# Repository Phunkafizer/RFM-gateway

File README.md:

<p align="center">

</p>

# RFM Gateway

RFM Gateway is a radio-to-WiFi bridge that connects HopeRF radio modules to an
ESP8266. It can receive RF data and forward it to your WiFi network, and it can
also send RF commands from HTTP or MQTT inputs.

Project description:
https://www.seegel-systeme.de/2023/09/15/rfm-wifi-gateway-a-radio-to-wifi-bridge/

Home Assistant forum:
https://community.home-assistant.io/t/rfm-gateway-a-sub-ghz-bridge-to-home-assistant/982886

## Highlights

- USB-C for power, flashing, and UART access
- Integrated USB programmer (no extra external programmer required)
- SMA antenna connector for the radio module
- Optional 0.96 inch I2C OLED support
- I2C and 1-wire extension headers

## Firmware capabilities

- 433 MHz RC pulse gateway (receive and transmit)
- 868 MHz sensor gateway (for supported sensor families)
- 868 MHz FS20 gateway
- Home Assistant integration via MQTT discovery

## Typical applications

- Bring wireless weather sensors into WiFi and MQTT
- Control RF sockets and remote controls
- Bridge RF nodes into home automation systems

## Repository structure

- [Firmware/](Firmware/): PlatformIO firmware project and web UI
- [custom_components/rfm_gateway/](custom_components/rfm_gateway/): Home Assistant custom integration
- [PCB/](PCB/): hardware design files
- [assets/](assets/): screenshots and images

## Home Assistant custom integration

The RFM Gateway integration connects Home Assistant directly to the gateway's
local HTTP API and provides a radio frequency transmitter. MQTT is not required
for this integration.

### Requirements

- Home Assistant 2026.5.0 or newer
- A gateway reachable from Home Assistant over the local network
- Firmware exposing `GET /api/rf/capabilities` and `POST /api/rf/transmit`
  (implemented by the RC pulse application in this repository)
- A radio module and antenna suitable for the devices you want to control

Compatibility depends on the firmware's RF API, not only its version number.
Check `http://<gateway-host>/api/rf/capabilities` for a JSON response containing
`supported_frequency_ranges` and `supported_modulations`. Replace
`<gateway-host>` with the gateway's hostname or IP address; include the port if
it is not 80.

### Installation

The repository can be added by link; being listed in the default catalog is not
required.

**Home Assistant 2026.11 and newer (Marketplace):**

1. Open **Settings > Marketplace > Add from link**.
2. Enter `https://github.com/Phunkafizer/RFM-gateway`.
3. Connect GitHub if prompted, and select **Integration** if asked for the type.
4. Open **RFM Gateway**, select **Install**, and continue with its setup flow.

**Home Assistant 2026.5 through 2026.10 (HACS):**

1. Install [HACS](https://www.hacs.xyz/docs/use/) if it is not already installed.
2. In HACS, open **Custom repositories** and add
   `https://github.com/Phunkafizer/RFM-gateway` with category **Integration**.
3. Download **RFM Gateway** and restart Home Assistant.
4. Open **Settings > Devices & services > Add integration**, then search for
   **RFM Gateway**.

**Manual installation:**

1. Copy the complete [custom_components/rfm_gateway/](custom_components/rfm_gateway/)
   folder into `<config>/custom_components/rfm_gateway/`, where `<config>` is
   the Home Assistant configuration directory.
2. Restart Home Assistant.
3. Open **Settings > Devices & services > Add integration** and select
   **RFM Gateway**.

When installing a release, make sure it contains the root-level
`custom_components/rfm_gateway/` folder and `hacs.json`. Older firmware-only
releases may not contain this layout.

### Configuration

Gateways advertising the matching `_http._tcp.local.` service and RF API
properties can be discovered automatically. Open **Settings > Devices &
services**, select the discovered gateway, and confirm setup.

For manual setup, enter:

| Setting | Description |
| --- | --- |
| Host | Gateway hostname or IP address, without `http://` or an API path |
| Port | HTTP API port; defaults to `80` |

Setup queries the gateway's capabilities before creating the integration.
No MQTT credentials or HTTP authentication settings are required.

### Supported functions and limitations

- Creates one radio frequency transmitter entity for each configured gateway.
- Sends raw RF commands through the gateway's HTTP transmit endpoint.
- Uses frequency ranges and modulations reported by the gateway.
- Can be used by compatible Home Assistant RF device integrations; it does not
  automatically create entities for every nearby RF device.
- This custom integration does not provide RF reception, sensor decoding, or
  MQTT discovery. The firmware's MQTT features are separate.
- Communication uses unencrypted local HTTP. Keep the gateway on a trusted
  network and do not expose its API to the internet.
- The transmitter becomes unavailable after a failed transmission and becomes
  available again after a successful transmission; it is not periodically polled.

### Troubleshooting

- **Cannot connect:** check the hostname/IP, HTTP port, gateway power, and network
  access from the machine running Home Assistant.
- **Invalid response:** check the capabilities URL above and ensure the firmware
  exposes the required RF API with valid capability data.
- **Transmit failure or unsupported modulation:** verify the gateway's reported
  capabilities and the radio module, antenna, and target-device protocol.
- **Not discovered:** add the gateway manually. Multicast discovery may not work
  across VLANs or routed networks.

For integration errors, check Home Assistant's logs under **Settings > System >
Logs** and report problems in the
[issue tracker](https://github.com/Phunkafizer/RFM-gateway/issues).

### Updates and removal

Install integration updates through Marketplace or HACS and restart Home
Assistant when prompted. For manual installations, replace the integration
folder with the new version and restart.

To remove a gateway, open its entry under **Settings > Devices & services** and
delete it. To remove the integration's files, also uninstall it in Marketplace
or HACS, or delete `<config>/custom_components/rfm_gateway/` for a manual
installation, then restart Home Assistant.

## Licensing

This repository uses a split-license model:

- Software/Firmware code: MIT, see [LICENSE](LICENSE)
- Hardware design files: CERN-OHL-S-2.0, see [LICENSE-HARDWARE](LICENSE-HARDWARE)
- Documentation and media assets: CC BY-SA 4.0, see [LICENSE-DOCS](LICENSE-DOCS)

### Preview

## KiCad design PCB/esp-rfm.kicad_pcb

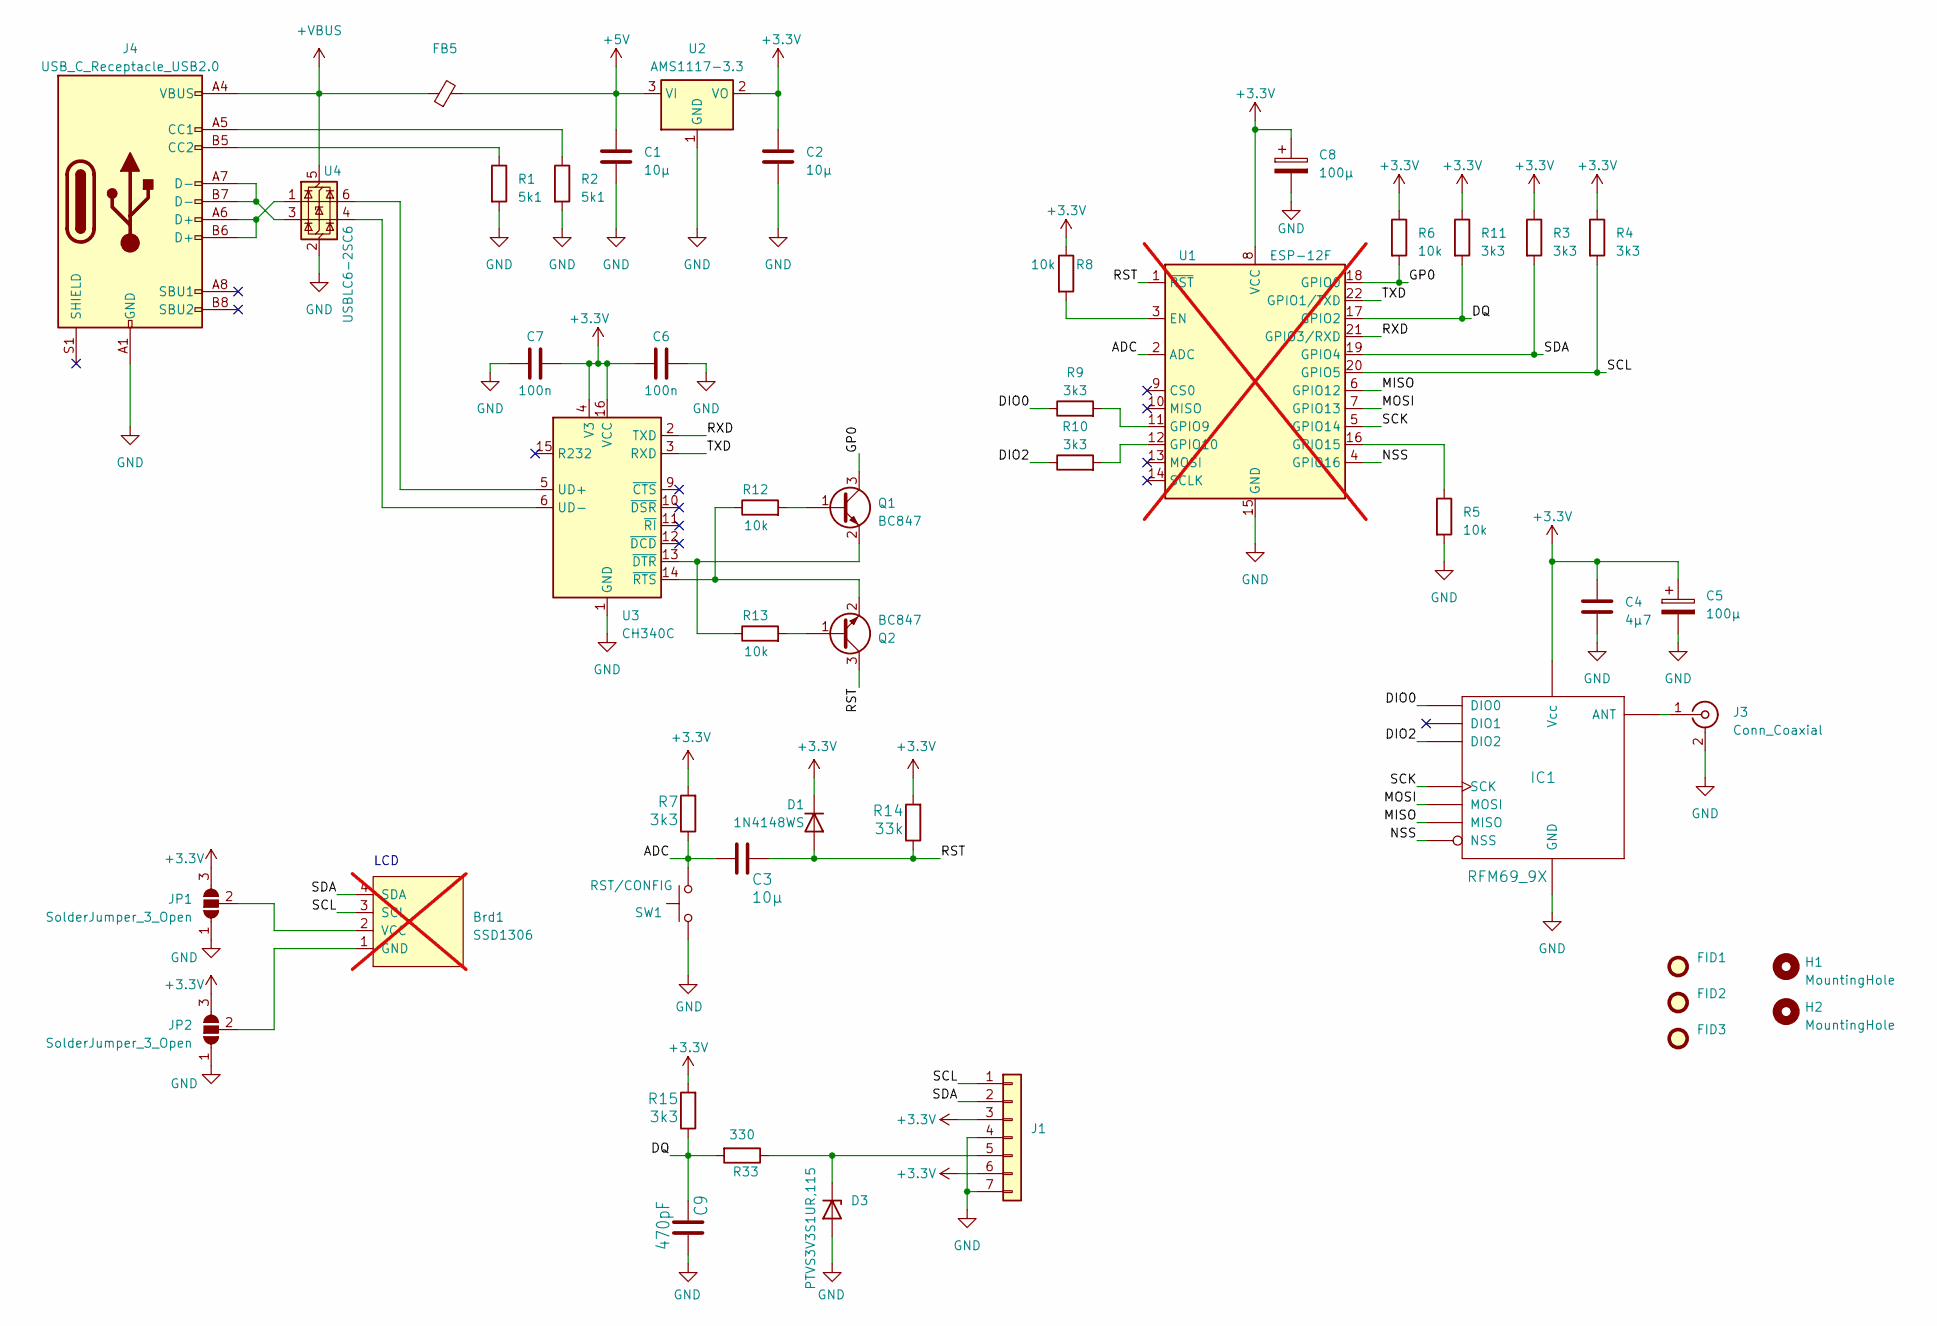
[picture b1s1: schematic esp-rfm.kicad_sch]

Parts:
Brd1: SSD1306; 128x64OLED; not fitted
C1, C2: 10µ; C_0805_2012Metric; LCSC C90543
C3: 10µ; C_0805_2012Metric; LCSC C15850
C4: 4µ7; C_0805_2012Metric; LCSC C319192
C5, C8: 100µ; CP_Elec_6.3x5.4; LCSC C59937
C6, C7: 100n; C_0805_2012Metric; LCSC C344180
C9: 470pF; C_0805_2012Metric; LCSC C62771
D1: 1N4148WS; D_SOD-323; LCSC C57759
D3: PTVS3V3S1UR,115; D_SOD-123; LCSC C183521
FB5: L_0603_1608Metric; LCSC C1002
FID1, FID2, FID3: Fiducial_1mm_Mask2mm
H1, H2: MountingHole; MountingHole_2.5mm_Pad
IC1: RFM69_9X
J1: PinHeader_1x07_P2.54mm_Vertical; LCSC C32713273
J3: Conn_Coaxial; SMA_H
J4: USB_C_Receptacle_USB2.0; USB_C_Receptacle_G-Switch_GT-USB-7010ASV; LCSC C2927037
JP1, JP2: SolderJumper_3_Open; SolderJumper-3_P1.3mm_Open_RoundedPad1.0x1.5mm
Q1, Q2: BC847; SOT-23; LCSC C181141
R1, R2: 5k1; R_0805_2012Metric; LCSC C431925
R3, R4, R7, R9, R10, R11, R15: 3k3; R_0805_2012Metric; LCSC C26010
R5, R6, R8, R12, R13: 10k; R_0805_2012Metric; LCSC C110775
R14: 33k; R_0805_2012Metric; LCSC C17633
R33: 330; R_0805_2012Metric; LCSC C17630
SW1: RST/CONFIG; SW_Tactile_SPST_Angled_PTS645Vx39-2LFS; LCSC C2837540
U1: ESP-12F; ESP-12E; LCSC C82891; not fitted
U2: AMS1117-3.3; SOT-223-3_TabPin2; LCSC C351784
U3: CH340C; SOIC-16_3.9x9.9mm_P1.27mm; LCSC C84681
U4: USBLC6-2SC6; SOT-23-6; LCSC C2827654

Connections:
+3.3V: C2.1, C4.1, C5.1, C6.1, C7.2, C8.1, D1.1 (K), IC1.Vcc, J1.3, J1.6, JP1.3 (B), JP2.3 (B), R3.1, R4.1, R6.1, R7.2, R8.1, R11.1, R14.2, R15.2, U1.8 (VCC), U2.2 (VO), U3.4 (V3), U3.16 (VCC)
+5V: C1.1, FB5.2, U2.3 (VI)
+VBUS: FB5.1, J4.A4 (VBUS), J4.A9 (VBUS), J4.B4 (VBUS), J4.B9 (VBUS), U4.5 (VBUS)
/ADC: C3.2, R7.1, SW1.1, U1.2 (ADC)
/DIO0: IC1.DIO0, R9.1
/DIO2: IC1.DIO2, R10.1
/DQ: C9.1, R11.2, R15.1, R33.2, U1.17 (GPIO2)
/GP0: Q1.3 (C), R6.2, U1.18 (GPIO0)
/MISO: IC1.MISO, U1.6 (GPIO12)
/MOSI: IC1.MOSI, U1.7 (GPIO13)
/NSS: IC1.NSS, U1.4 (GPIO16)
/RST: C3.1, D1.2 (A), Q2.3 (C), R14.1, U1.1 (~RST)
/RXD: U1.21 (GPIO3/RXD), U3.2 (TXD)
/SCK: IC1.SCK, U1.5 (GPIO14)
/SCL: Brd1.3 (SCL), J1.1, R4.2, U1.20 (GPIO5)
/SDA: Brd1.4 (SDA), J1.2, R3.2, U1.19 (GPIO4)
/TXD: U1.22 (GPIO1/TXD), U3.3 (RXD)
GND: C1.2, C2.2, C4.2, C5.2, C6.2, C7.1, C8.2, C9.2, D3.2 (A), IC1.2.1 (GND), IC1.2.8 (GND), IC1.2.10 (GND), IC1.GND, J1.4, J1.7, J3.2 (Ext), J4.A1 (GND), J4.A12 (GND), J4.B1 (GND), J4.B12 (GND), JP1.1 (A), JP2.1 (A), R1.2, R2.2, R5.2, SW1.2, U1.15 (GND), U2.1 (GND), U3.1 (GND), U4.2 (GND)
unnamed: Brd1.1 (GND), JP2.2 (C)
unnamed: Brd1.2 (VCC), JP1.2 (C)
unnamed: D3.1 (K), J1.5, R33.1
unnamed: IC1.ANT, J3.1 (In)
unnamed: J4.A5 (CC1), R2.1
unnamed: J4.B5 (CC2), R1.1
unnamed: J4.A6 (D+), J4.B6 (D+), U4.1 (I/O1)
unnamed: J4.A7 (D-), J4.B7 (D-), U4.3 (I/O2)
unnamed: Q1.1 (B), R12.2
unnamed: Q1.2 (E), R13.1, U3.13 (~DTR)
unnamed: Q2.1 (B), R13.2
unnamed: Q2.2 (E), R12.1, U3.14 (~RTS)
unnamed: R8.2, U1.3 (EN)
unnamed: R9.2, U1.11 (GPIO9)
unnamed: R10.2, U1.12 (GPIO10)
unnamed: R5.1, U1.16 (GPIO15)
unnamed: U3.5 (UD+), U4.6 (I/O1)
unnamed: U3.6 (UD-), U4.4 (I/O2)

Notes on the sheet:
LCD

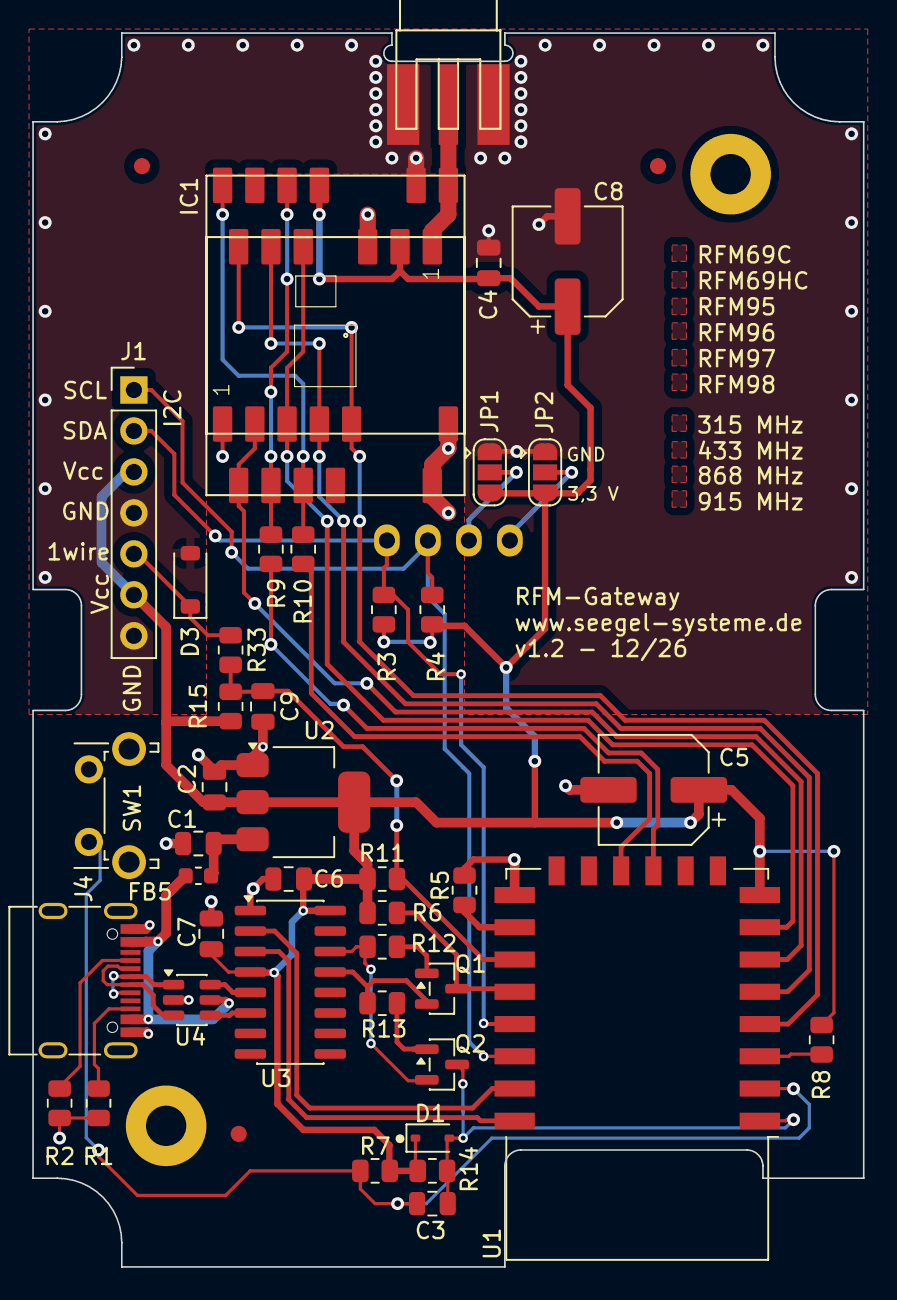
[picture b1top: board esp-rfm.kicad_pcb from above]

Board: 2 copper layers, 51.5 x 76.5 mm, 47 parts (1 on the bottom side), 36 nets.

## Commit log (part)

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2024-07-04 init commit
2024-08-19 add radio applications cleanup
2024-09-17 add slider for TX power fix RFM69 initialization
2024-12-09 Add factory reset
2025-01-13 fix warning in platformio.ini
    status LED blinker
    update PCB
2025-02-10 add helpers & testtools fix radiomodel in webUI
2026-01-29 fix FS20 codec add home assistant auto discovery add RX threshold setting
2026-01-30 webUI add websocket status fix sync IT32
2026-01-31 fix FS20 ext command add auto discovery buttons
2026-02-01 add more options for FS20 MQTT JSON payload
2026-02-03 fix pilota encoder
2026-02-04 HA auto discovery for 868 MHz sensors
2026-02-08 set HA availability show HA discovery button on send
2026-03-29 minify html before build testrfm: send default config fix RC433 codecs in webUI
2026-04-05 add tab in webUI for sending RC433 codes add build yml
2026-04-05 add permissions
2026-04-11 add custom RX mode for 868 gateway add import / export to webUI add frequency setting
2026-04-11 change pin header add ferrite
2026-04-11 add github action fix frequency setting
2026-04-11 add toast
2026-04-11 eye candy
2026-04-11 check tag
2026-04-11 improve log visibility seperate command buttons
2026-04-12 lower DCC frequency add RX BW constants add test & setup tools
2026-04-12 include sdr in testapp
2026-04-12 show toast on discovery button add HA sensor for battery low eye candy
2026-04-12 add badges and links
2026-04-12 add license
2026-04-12 update license badge
2026-04-13 add configurable hostname eye candy autocalibration in setup tool txtest sends CW signal
2026-05-17 add frequency and timebase to API
2026-05-17 adjust timing for NEXA
2026-06-10 add production helper add HA integration add tools

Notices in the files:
README.md:
License: MIT | CERN-OHL-S-2.0 | CC BY-SA 4.0
